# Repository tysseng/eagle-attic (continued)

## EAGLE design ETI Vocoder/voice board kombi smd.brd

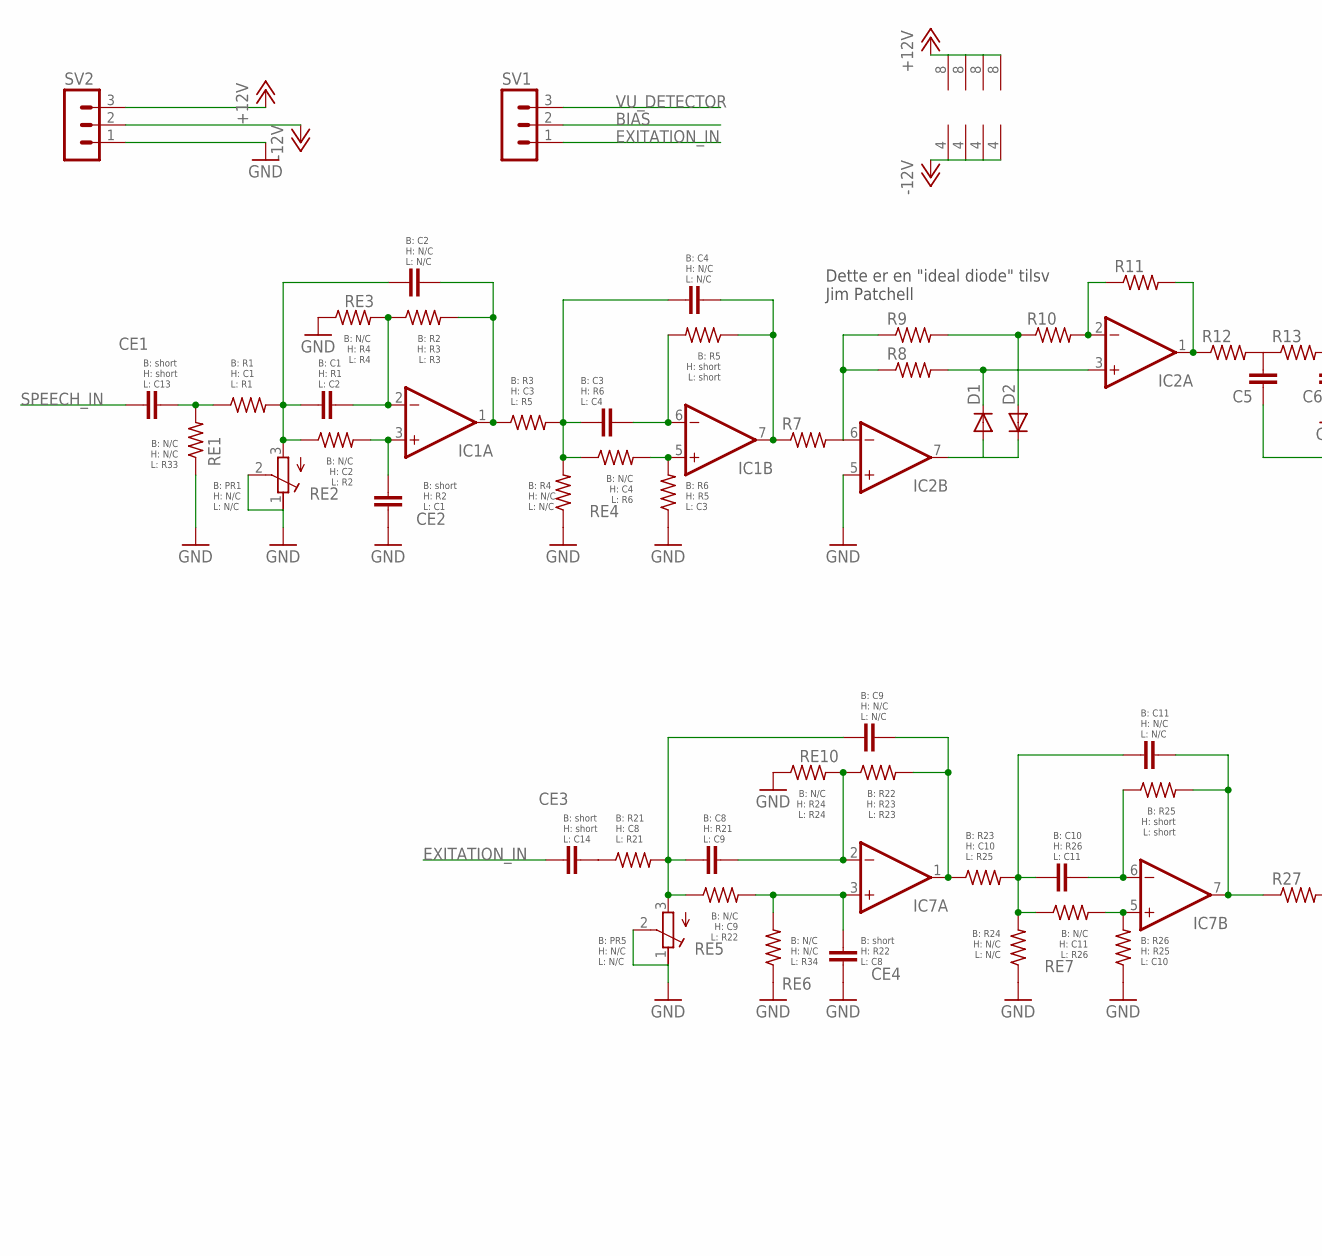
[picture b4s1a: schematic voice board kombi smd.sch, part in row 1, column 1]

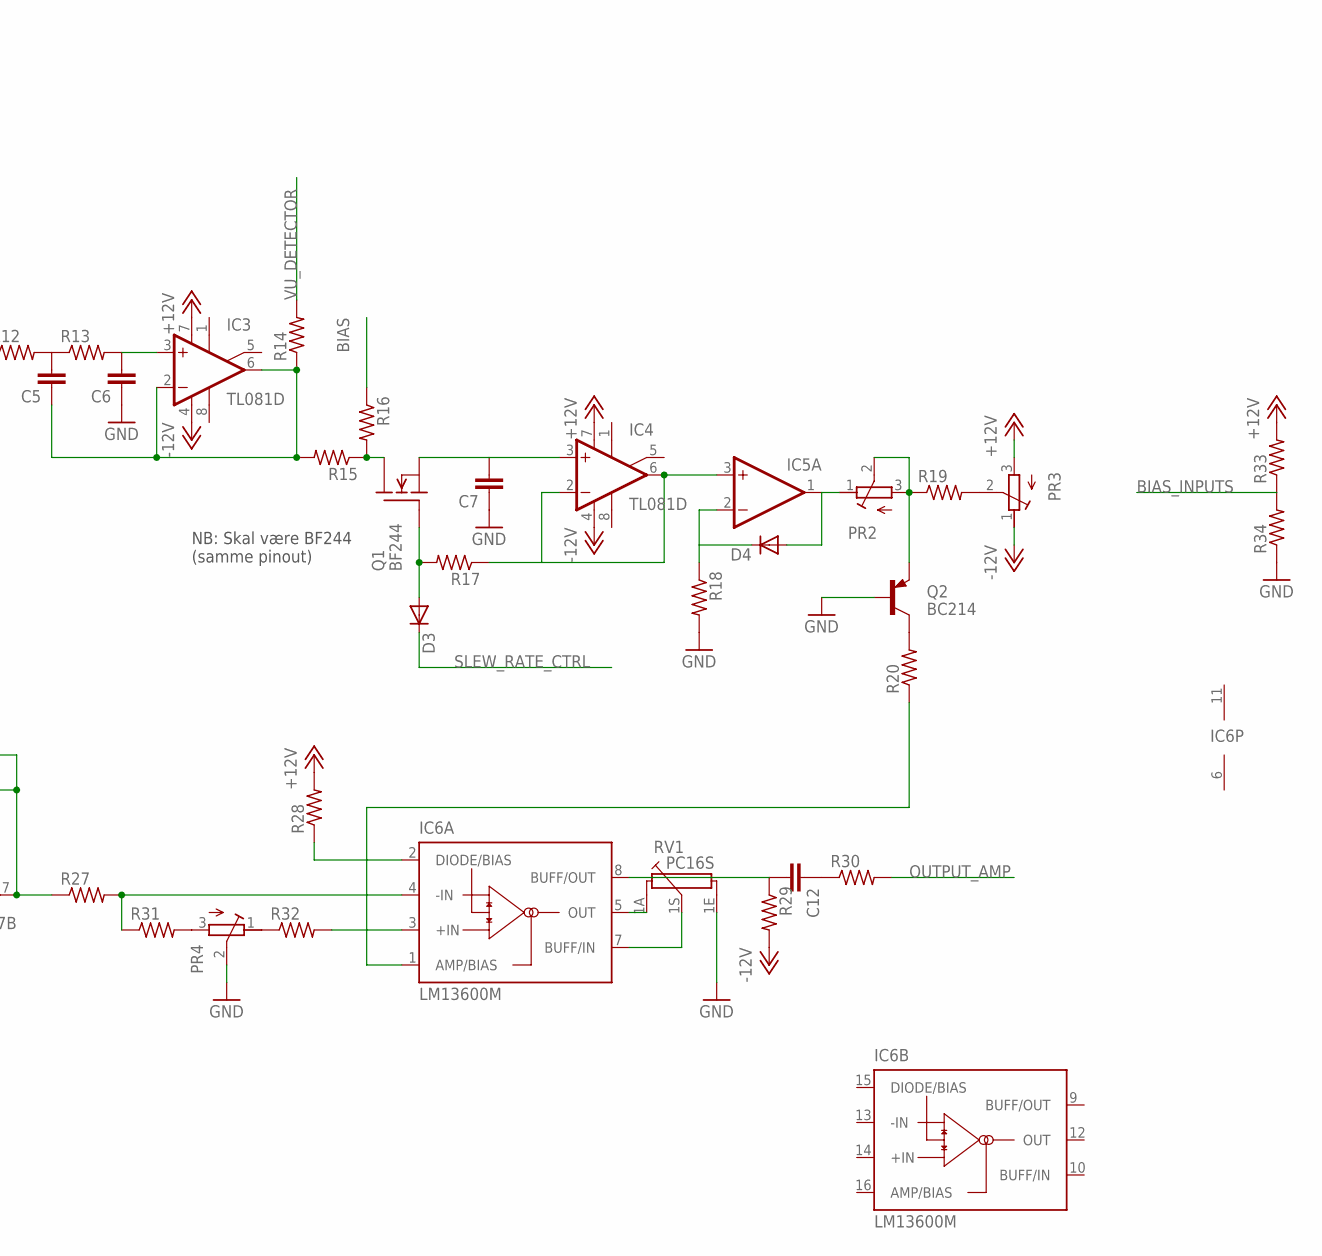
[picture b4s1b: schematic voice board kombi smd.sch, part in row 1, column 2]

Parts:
C1, C2, C3, C4, C5, C6, C7, C8, C9, C10, C11, C12: C-EUC0805; C0805
CE1, CE2, CE3, CE4: C-EUC0805; C0805
D1, D2, D3, D4: DIODE-SOD80C; SOD80C
IC1, IC2, IC5, IC7: TL072D; SO08
IC3, IC4: TL081D; SO08
IC6: LM13600M; SO16
PR1, PR2, PR3, PR4, PR5: R-TRIMMT93XA; RTRIMT93XA
Q1: BF244; TO-92
Q2: BC214; TO92
R1, R2, R3, R4, R5, R6, R7, R8, R9, R10, R11, R12, R13, R14, R15, R16, R17, R18, R19, R20, R21, R22, R23, R24, R25, R26, R27, R28, R29, R30, R31, R32, R33, R34: R-US_R0805; R0805
RE1, RE2, RE3, RE4, RE5, RE6, RE7, RE10: R-US_R0805; R0805
RV1: PC16S
SV1, SV2: MA03-1

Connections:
+12V: IC1.8 (V+), IC2.8 (V+), IC3.7 (V+), IC4.7 (V+), IC5.8 (V+), IC7.8 (V+), PR3.3 (A), R28.2, R33.2, SV2.3
-12V: IC1.4 (V-), IC2.4 (V-), IC3.4 (V-), IC4.4 (V-), IC5.4 (V-), IC7.4 (V-), PR3.1 (E), R29.2, SV2.2
BIAS: R16.1, SV1.2
BIAS_INPUTS: R33.1, R34.2
EXITATION_IN: CE3.1, SV1.1
GND: C6.1, C7.1, CE2.1, CE4.1, IC2.5 (+IN), PR1.1 (E), PR1.2 (S), PR4.2 (S), PR5.1 (E), PR5.2 (S), Q2.2 (B), R4.1, R6.1, R18.2, R24.1, R26.1, R34.1, RE1.1, RE3.1, RE6.1, RE10.1, RV1.1E, SV2.1
unnamed: C1.2, IC1.2 (-IN), R2.1, RE3.2
unnamed: C1.1, C2.1, PR1.3 (A), R1.2, RE2.1
unnamed: C2.2, IC1.1 (OUT), R2.2, R3.1
unnamed: IC2.6 (-IN), R7.2, R8.1, R9.1
unnamed: C3.1, C4.1, R3.2, R4.2, RE4.1
unnamed: C3.2, IC1.6 (-IN), R5.2
unnamed: IC1.5 (+IN), R6.2, RE4.2
unnamed: C4.2, IC1.7 (OUT), R5.1, R7.1
unnamed: D1.C, IC2.3 (+IN), R8.2
unnamed: D1.A, D2.C, IC2.7 (OUT)
unnamed: D2.A, R9.2, R10.1
unnamed: IC2.2 (-IN), R10.2, R11.1
unnamed: IC2.1 (OUT), R11.2, R12.1
unnamed: C5.2, R12.2, R13.1
unnamed: C5.1, IC3.2 (-IN), IC3.6 (OUT), R14.1, R15.2
unnamed: C6.2, IC3.3 (+IN), R13.2
unnamed: Q1.3 (D), R15.1, R16.2
unnamed: C7.2, IC4.3 (+IN), Q1.1 (S)
unnamed: D3.A, Q1.2 (G), R17.2
unnamed: IC4.2 (-IN), IC4.6 (OUT), IC5.3 (+IN), R17.1
unnamed: D4.C, IC5.2 (-IN), R18.1
unnamed: D4.A, IC5.1 (OUT), PR2.1 (E)
unnamed: PR2.2 (S), PR2.3 (A), Q2.1 (E), R19.1
unnamed: PR3.2 (S), R19.2
unnamed: Q2.3 (C), R20.2
unnamed: PR4.3 (A), R31.2
unnamed: C8.2, C9.2, PR5.3 (A), R21.2, RE5.1
unnamed: C10.2, C11.2, R23.2, R24.2, RE7.1
unnamed: C8.1, IC7.2 (-IN), R22.1, RE10.2
unnamed: C9.1, IC7.1 (OUT), R22.2, R23.1
unnamed: C10.1, IC7.6 (-IN), R25.1
unnamed: IC7.5 (+IN), R26.2, RE7.2
unnamed: C12.2, IC6.8 (BUFF/OUT), R29.1
unnamed: C12.1, R30.1
unnamed: C11.1, IC7.7 (OUT), R25.2, R27.1
unnamed: PR4.1 (E), R32.1
unnamed: IC6.3 (+IN), R32.2
unnamed: IC6.2 (DIODE/BIAS), R28.1
unnamed: IC6.4 (-IN), R27.2, R31.1
unnamed: IC6.1 (AMP/BIAS), R20.1
unnamed: IC6.5 (OUT), RV1.1A
unnamed: IC6.7 (BUFF/IN), RV1.1S
unnamed: CE1.2, R1.1, RE1.2
unnamed: CE2.2, IC1.3 (+IN), RE2.2
unnamed: CE3.2, R21.1
unnamed: CE4.2, IC7.3 (+IN), RE5.2, RE6.2
OUTPUT_AMP: R30.2
SLEW_RATE_CTRL: D3.C
SPEECH_IN: CE1.1
V+: IC6.11 (V+)
V-: IC6.6 (V-)
VU_DETECTOR: R14.2, SV1.3

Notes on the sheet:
NB: Skal være BF244 (samme pinout)
Dette er en "ideal diode" tilsv Jim Patchell
B: short H: short L: C13
B: R1 H: C1 L: R1
B: PR1 H: N/C L: N/C
B: C1 H: R1 L: C2
B: C2 H: N/C L: N/C
B: C4 H: N/C L: N/C
B: R2 H: R3 L: R3
B: R3 H: C3 L: R5
B: R4 H: N/C L: N/C
B: C3 H: R6 L: C4
B: R6 H: R5 L: C3
B: R5 H: short L: short
B: N/C H: R4 L: R4
B: short H: R2 L: C1
B: N/C H: C2 L: R2
B: N/C H: N/C L: R33
B: short H: short L: C14
B: R21 H: C8 L: R21
B: C8 H: R21 L: C9
B: R22 H: R23 L: R23
B: C9 H: N/C L: N/C
B: C10 H: R26 L: C11
B: R23 H: C10 L: R25
B: N/C H: N/C L: R34
B: R24 H: N/C L: N/C
B: R26 H: R25 L: C10
B: C11 H: N/C L: N/C
B: R25 H: short L: short
B: N/C H: C9 L: R22
B: short H: R22 L: C8
B: N/C H: C4 L: R6
B: N/C H: C11 L: R26
B: PR5 H: N/C L: N/C
B: N/C H: R24 L: R24

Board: 2 copper layers, 79 parts (0 on the bottom side), 53 nets, no tracks yet.
